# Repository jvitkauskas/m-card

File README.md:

# m-card

A small add-on board (30 × 25.2 mm) that gives the **M-VAVE FM-1 or SMK-37** a microSD card slot. **No soldering to the FM-1 or SMK-37 is
needed.** The board sits under the audio jacks and plugs in between the FM-1's LCD and its main board, so the card
shares the LCD's SPI bus.

| Top | Bottom |
|---|---|
|  |  |

## I just want to order a board

Everything you need is already in this repository. You don't have to install KiCad or run anything.

### 1. Order the PCB

Upload [`fab/m-card-gerbers.zip`](fab/m-card-gerbers.zip) to [JLCPCB](https://jlcpcb.com) or any other PCB maker that
takes Gerbers. The size (30 × 25.2 mm) is read from the files, and the design rules are standard (0.2 mm tracks and
spacing, 0.3 mm holes), so the default settings work. Two are worth a look:

| Setting | Choice | Notes |
|---|---|---|
| Layers | 2 | |
| Surface finish | HASL (lead-free or with lead) | The cheap default, and the easiest to hand-solder. ENIG has flatter pads, but it's optional and often costs several times more. OSP is fine if you'll solder the boards soon, since it doesn't keep well. |

### 2. Buy the parts

All parts are in stock at [LCSC](https://www.lcsc.com). Search for the part numbers below. A few spares of the
small resistors and capacitors are handy.

| Qty | Refs | Part | LCSC |
|---|---|---|---|
| 1 | J1 | Hirose DM3CS-SF, hinged microSD socket | C202111 |
| 1 | J2 | XUNPU FPC-05F-10PH20, 10-pin 0.5 mm FPC socket, **bottom** contact | C2856798 |
| 1 | J3 | XUNPU FPC-0.5AS-10PWBH20, 10-pin 0.5 mm FPC socket, **top** contact | C3446068 |
| 1 | U1 | 74LVC1G04 inverter, SOT-23-5 (TI SN74LVC1G04DBVR) | C7827 |
| 5 | R2, R3, R4, R7, R8 | 47 kΩ, 0805 | C17713 |
| 2 | R5, R6 | 470 Ω, 0805 | C17710 |
| 1 | R1 | 150 Ω, 0805 | C17471 |
| 1 | C1 | 10 µF, 0805 | C15850 |
| 1 | C2 | 100 nF, 0805 | C49678 |
| 1 | | 10-pin, 0.5 mm pitch FFC cable, about 80 mm, contacts on the same side at both ends ("type A") | |
| | | Thin double-sided tape | |

You also need a microSD card.

The FFC cable runs from the FM-1's J12 to the board's J2. The cable type and length are what the first build is
planned with: please report back if they don't work.

### 3. Solder it

Print [`docs/assembly.pdf`](docs/assembly.pdf). It shows every part's position and value at 5:1, which way round
the parts go, and a good order to solder them in.

- Every part is hand-solderable with a fine-tip iron. The 0805 and SOT-23-5 parts use extra-long pads.
- The two FPC sockets (J2, J3) are the fiddly part, at 0.5 mm pitch. Use plenty of flux, tack one tab, drag-solder the
  row, and wick off any bridges.
- **Before you install it:** check with a multimeter that 3.3 V (J2 line 7) is not shorted to GND (line 1), and that
  each J2 line beeps through to the same J3 line.

### 4. Install it

[`docs/template-1to1.pdf`](docs/template-1to1.pdf) is a 1:1 paper template. Print it at 100 % ("actual size"), check
its 50 mm scale bars with a ruler, cut out the board outline, and lay it in the FM-1 to see where the board goes.

1. Open the FM-1 and disconnect the battery.
2. Unplug the LCD's cable from J12 on the FM-1's main board, and plug it into the board's **J3** (contacts up).
3. Connect the FM-1's J12 to the board's **J2** with the short FFC cable (contacts down at J2).
4. Tape the board down under the audio jacks, with J3 right below the gap between the two jacks.

The silkscreen next to each socket repeats which way the cable's contacts face, and marks the cable's line 1.

### Having JLC assemble it instead

Enable "PCB Assembly" and choose "Assemble top side". [`fab/bom.csv`](fab/bom.csv) and [`fab/cpl.csv`](fab/cpl.csv) are
the parts list and placement file in JLC's format. Before you pay, check every part's rotation in JLC's placement preview:
their library sometimes disagrees with KiCad's. J1, J2 and J3 are "extended" parts at JLC, which adds a small fee per part type.

## How it works

The FM-1's LCD is driven over SPI through the 10-pin connector J12. The board passes all ten lines straight from J2
to J3, and the card taps four of them:

| J12 line | Signal | On the card side |
|---|---|---|
| 2 | MISO (shared with the LCD's D/C) | → 150 Ω → card DO (DAT0), 47k pull-up |
| 3 | LCD chip select | → 74LVC1G04 inverter → card CS: the card is selected whenever the LCD isn't. 47k pull-down keeps the card deselected during reset. |
| 4 | CLK | → 470 Ω → card CLK |
| 5 | MOSI | → 470 Ω → card DI (CMD), 47k pull-up |
| 7 | 3.3 V | → card power, 10 µF + 100 nF |
| 1, 10 | GND | |

DAT1 and DAT2 have 47k pull-ups. The series resistors limit the current if the MCU and the card ever drive a line at
the same time, and they set a ceiling on the SPI clock. Firmware should start the card slowly and raise the clock
only once reads come back with good checksums.

### R1 and the card's speed (v1.1)

R1 is what limits how fast an FM-1 can read the card: the card's DO goes through it into the LCD's D/C line, which
has a capacitor to ground on the FM-1's board. v1.0 boards have 220 Ω there, and with it an FM-1 reads its card
cleanly at up to 9.6 MHz but not at 12, so the m-apps driver settles at 8 MHz. From v1.1 it's 150 Ω, and the FM-1
reads at 12 MHz: in tests, 256 MiB read with no errors, and USB disk mode went from 724 to about 850 KB/s. An SMK-37
read up to 16 MHz with it. The m-apps driver runs the card at 12 MHz on both.

To speed up a v1.0 board, replace R1 with 150 Ω, or solder a 510 Ω on top of it (220 ∥ 510 ≈ 154 Ω, tested on both
units). Don't go much lower: R1 also limits the current if the card and the FM-1 ever drive that line at once.

## Changing the design

The board is generated from Python, so there are no hand-drawn parts. You need KiCad 9 (its `pcbnew` Python module
and `kicad-cli`). Routing uses [Freerouting](https://github.com/freerouting/freerouting) 1.9.

```sh
python3 make_board.py place       # parts, nets, outline -> m-card.kicad_pcb and m-card.dsn
xvfb-run -a java -jar freerouting.jar -de m-card.dsn -do m-card.ses -mp 100   # autoroute
python3 make_board.py finish      # import the routes, add ground stitching vias and pours
python3 make_board.py fab         # design-rule check, then fab/: Gerber zip, bom.csv, cpl.csv
python3 make_board.py render      # docs/render-*.png (fetches KiCad's 3D models into 3d/)
python3 make_assembly.py          # docs/assembly.pdf
python3 make_template.py          # docs/template-1to1.pdf
```

Positions in `make_board.py` are in millimetres on the FM-1 board's back side: across from its left edge, and up from
its bottom edge.

The connector footprints (J1, J2, J3) are generated in `make_board.py` from the makers' datasheet land patterns. The
resistors, capacitors and U1 use KiCad's standard footprints.

## Licence

Everything here (the scripts, the board, the generated files) is dedicated to the public domain under
[CC0 1.0](LICENSE).

KiCad's standard footprints are CC-BY-SA 4.0 with an exception that leaves designs using them free to be licensed any
way. The 3D models that `render` downloads are KiCad's too, under the same terms. They're only used for the pictures
and aren't part of this repository.

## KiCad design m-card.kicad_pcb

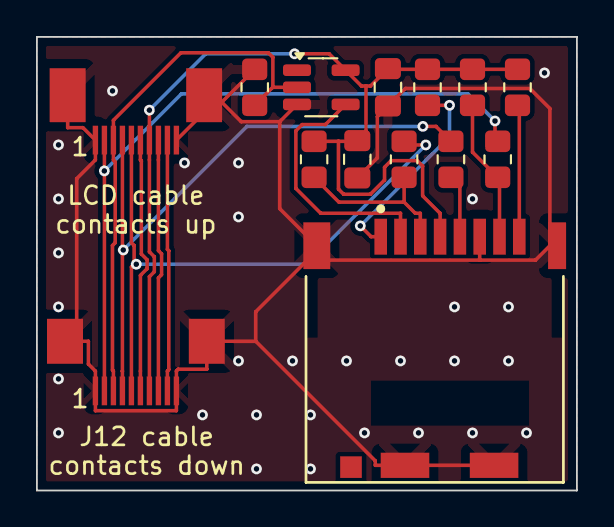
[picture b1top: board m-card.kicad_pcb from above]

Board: 2 copper layers, 30.0 x 25.2 mm, 14 parts (0 on the bottom side), 15 nets.

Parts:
C1: 10uF; C_0805_2012Metric_Pad1.18x1.45mm_HandSolder
C2: 100nF; C_0805_2012Metric_Pad1.18x1.45mm_HandSolder
J1: microSD hinged (Hirose DM3CS-SF); microSD_Hirose_DM3CS-SF_hinged
J2: FPC 10P 0.5 bottom contact; FPC_10P_0.5_XUNPU_FPC-05F-10PH20
J3: FPC 10P 0.5 top contact; FPC_10P_0.5_XUNPU_FPC-0.5AS-10PWBH20
R1: 150; R_0805_2012Metric_Pad1.20x1.40mm_HandSolder
R2, R3, R4, R7, R8: 47k; R_0805_2012Metric_Pad1.20x1.40mm_HandSolder
R5, R6: 470; R_0805_2012Metric_Pad1.20x1.40mm_HandSolder
U1: 74LVC1G04; SOT-23-5_HandSoldering

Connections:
3V3: C1.1, C2.1, J1.4, J2.4, J3.4, R2.1, R3.1, R7.1, R8.1, U1.5
CARD_CS: J1.2, U1.4
CLK: J2.7, J3.7, R5.1
DAT0: J1.7, R1.2, R7.2
DAT1: J1.8, R3.2
DAT2: J1.1, R2.2
GND: C1.2, C2.2, J1.6, J1.9, J2.1, J2.10, J2.11, J2.12, J3.1, J3.10, J3.11, J3.12, R4.2, U1.3
LCD_6: J2.5, J3.5
LCD_8: J2.3, J3.3
LCD_9: J2.2, J3.2
LCD_CS: J2.8, J3.8, R4.1, U1.2
MISO: J2.9, J3.9, R1.1
MOSI: J2.6, J3.6, R6.1
SD_CLK: J1.5, R5.2
SD_DI: J1.3, R6.2, R8.2

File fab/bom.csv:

Comment,Designator,Footprint,LCSC Part #
10uF,C1,C_0805_2012Metric_Pad1.18x1.45mm_HandSolder,C15850
100nF,C2,C_0805_2012Metric_Pad1.18x1.45mm_HandSolder,C49678
microSD hinged (Hirose DM3CS-SF),J1,microSD_Hirose_DM3CS-SF_hinged,C202111
FPC 10P 0.5 bottom contact,J2,FPC_10P_0.5_XUNPU_FPC-05F-10PH20,C2856798
FPC 10P 0.5 top contact,J3,FPC_10P_0.5_XUNPU_FPC-0.5AS-10PWBH20,C3446068
150,R1,R_0805_2012Metric_Pad1.20x1.40mm_HandSolder,C17471
470,"R5,R6",R_0805_2012Metric_Pad1.20x1.40mm_HandSolder,C17710
47k,"R2,R3,R4,R7,R8",R_0805_2012Metric_Pad1.20x1.40mm_HandSolder,C17713
74LVC1G04,U1,SOT-23-5_HandSoldering,C7827
